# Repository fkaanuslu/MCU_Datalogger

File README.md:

# MCU_Datalogger

Schematic Layout first page

Schematic Layout second page [Connectors.sch]

PCB Layout

3D view frontside

3D view backside

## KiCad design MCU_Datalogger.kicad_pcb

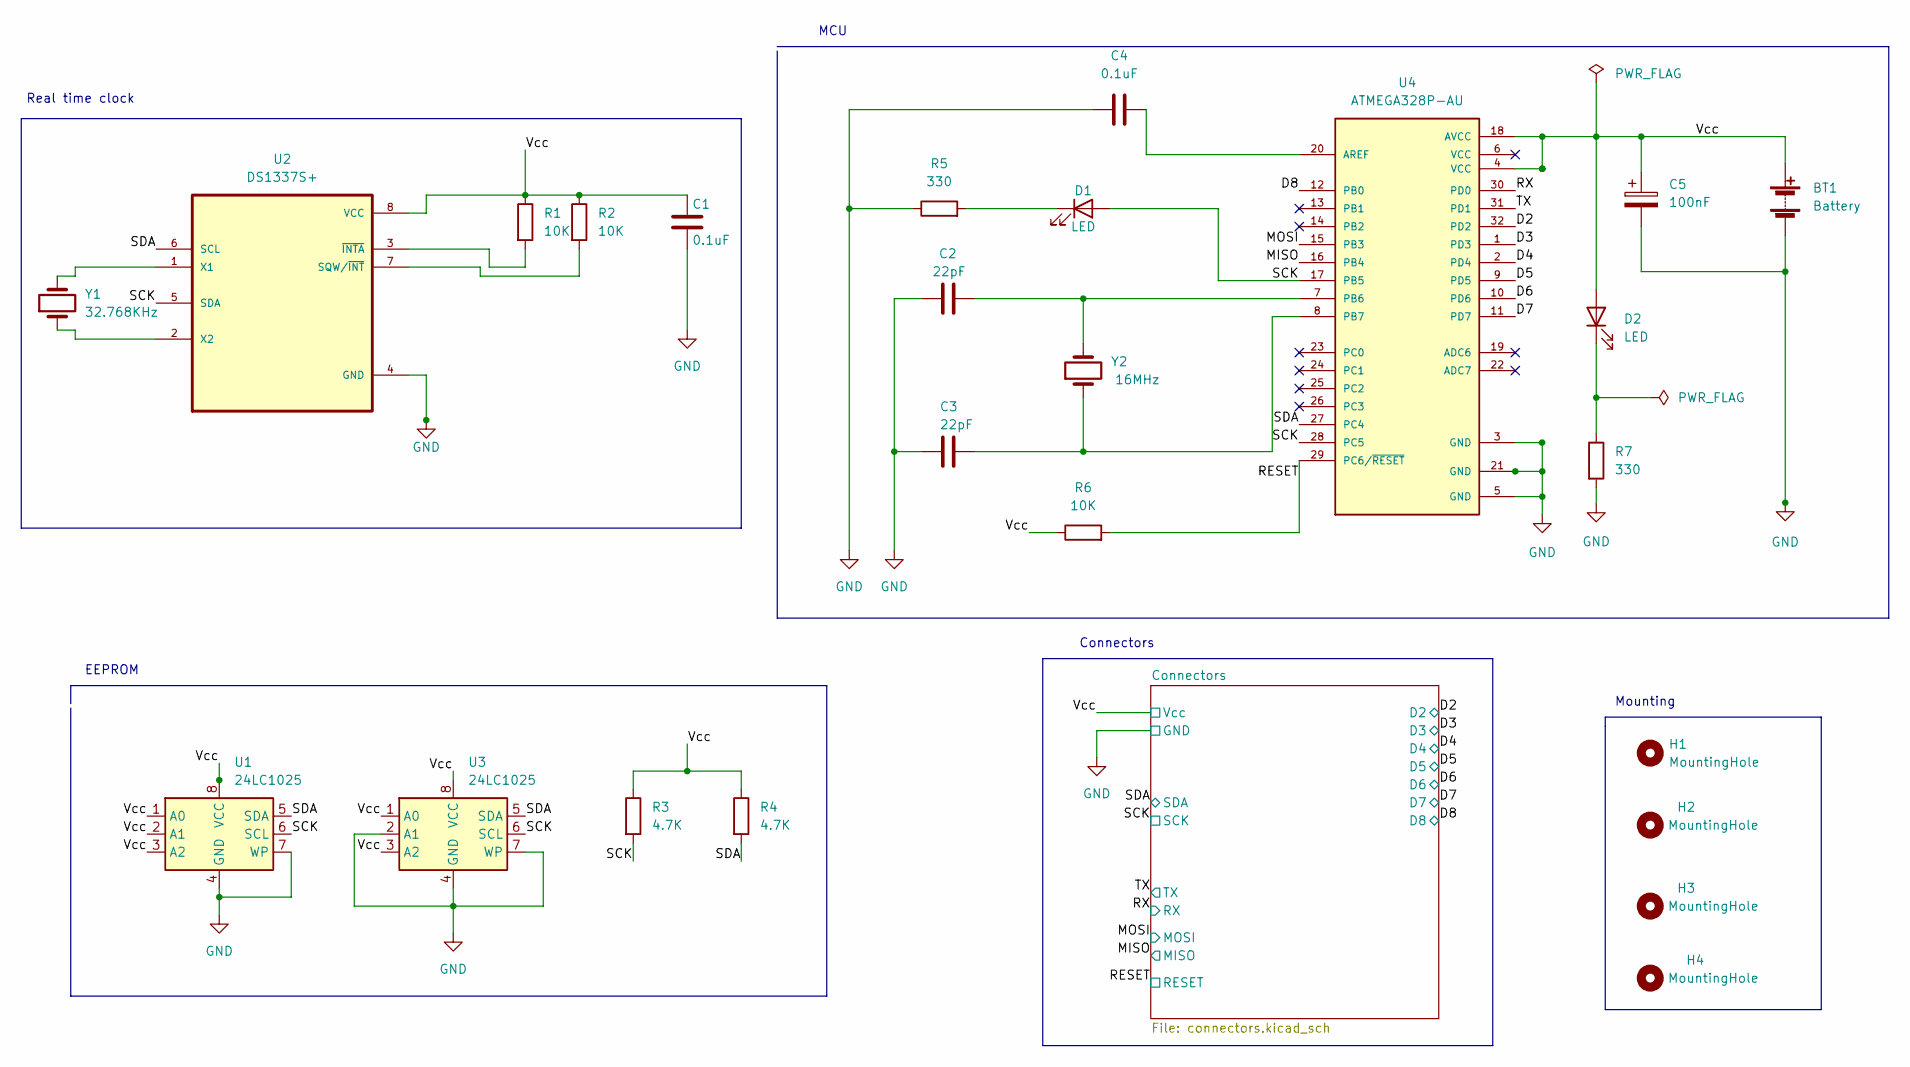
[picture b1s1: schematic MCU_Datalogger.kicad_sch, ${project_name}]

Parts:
BT1: Battery; PinHeader_1x02_P2.54mm_Vertical
C1, C4: 0.1uF; C_0805_2012Metric
C2, C3: 22pF; C_0805_2012Metric
C5: 100nF; C_0805_2012Metric
D1, D2: LED; LED_0805_2012Metric
H1, H2, H3, H4: MountingHole; MountingHole_2.1mm
R1, R2, R6: 10K; R_0805_2012Metric
R3, R4: 4.7K; R_0805_2012Metric
R5, R7: 330; R_0805_2012Metric
U1, U3: 24LC1025; SOIC-8_5.23x5.23mm_P1.27mm
U2: DS1337S+; SOIC127P600X175-8N
U4: ATMEGA328P-AU; QFP80P900X900X120-32N
Y1: 32.768KHz; Crystal_SMD_5032-2Pin_5.0x3.2mm_HandSoldering
Y2: 16MHz; Crystal_SMD_5032-2Pin_5.0x3.2mm_HandSoldering

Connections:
/D2: U4.32 (PD2); also elsewhere on the board
/D3: U4.1 (PD3); also elsewhere on the board
/D4: U4.2 (PD4); also elsewhere on the board
/D5: U4.9 (PD5); also elsewhere on the board
/D6: U4.10 (PD6); also elsewhere on the board
/D7: U4.11 (PD7); also elsewhere on the board
/D8: U4.12 (PB0); also elsewhere on the board
/MISO: U4.16 (PB4); also elsewhere on the board
/MOSI: U4.15 (PB3); also elsewhere on the board
/RESET: R6.2, U4.29 (PC6/~RESET); also elsewhere on the board
/RX: U4.30 (PD0); also elsewhere on the board
/SCK: D1.2 (A), R3.2, U1.6 (SCL), U2.5 (SDA), U3.6 (SCL), U4.17 (PB5), U4.28 (PC5); also elsewhere on the board
/SDA: R4.2, U1.5 (SDA), U2.6 (SCL), U3.5 (SDA), U4.27 (PC4); also elsewhere on the board
/TX: U4.31 (PD1); also elsewhere on the board
/Vcc: BT1.1 (+), C1.1, C5.1, D2.2 (A), R1.1, R2.1, R3.1, R4.1, R6.1, U1.1 (A0), U1.2 (A1), U1.3 (A2), U1.8 (VCC), U2.8 (VCC), U3.1 (A0), U3.3 (A2), U3.8 (VCC), U4.4 (VCC), U4.18 (AVCC); also elsewhere on the board
GND: BT1.2 (-), C1.2, C2.1, C3.2, C4.1, C5.2, R5.1, R7.2, U1.4 (GND), U1.7 (WP), U2.4 (GND), U3.2 (A1), U3.4 (GND), U3.7 (WP), U4.3 (GND), U4.5 (GND), U4.21 (GND); also elsewhere on the board
unnamed: C2.2, U4.7 (PB6), Y2.2
unnamed: C3.1, U4.8 (PB7), Y2.1
unnamed: C4.2, U4.20 (AREF)
unnamed: D1.1 (K), R5.2
unnamed: D2.1 (K), R7.1
unnamed: R1.2, U2.3 (~INTA)
unnamed: R2.2, U2.7 (SQW/~INT)
unnamed: U2.1 (X1), Y1.2
unnamed: U2.2 (X2), Y1.1

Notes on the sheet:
Real time clock
Mounting
MCU
EEPROM
Connectors

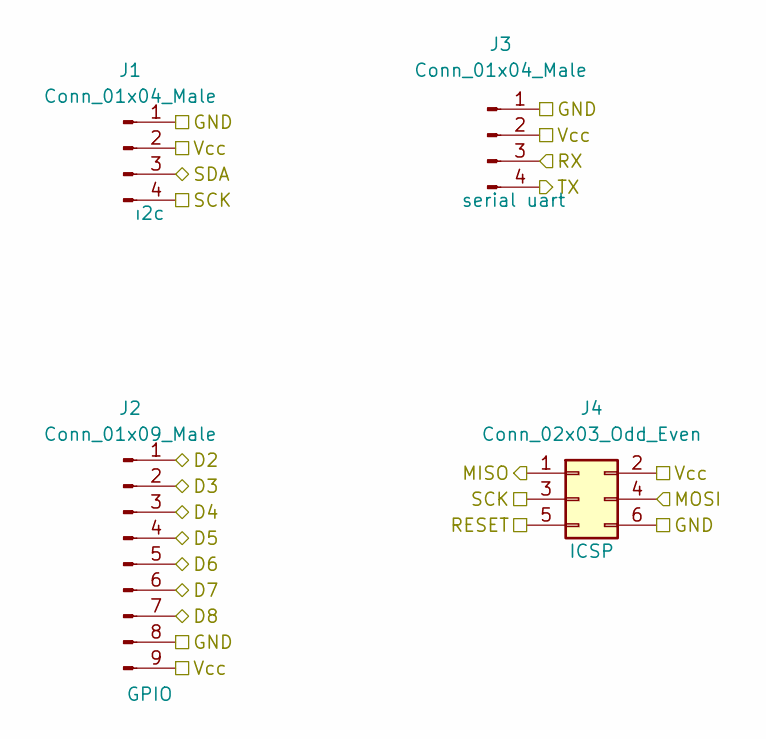
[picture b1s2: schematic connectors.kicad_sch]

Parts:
J1, J3: Conn_01x04_Male; PinHeader_1x04_P2.54mm_Vertical
J2: Conn_01x09_Male; PinHeader_1x09_P2.54mm_Vertical
J4: Conn_02x03_Odd_Even; PinHeader_2x03_P2.54mm_Vertical

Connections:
/D2: J2.1; also elsewhere on the board
/D3: J2.2; also elsewhere on the board
/D4: J2.3; also elsewhere on the board
/D5: J2.4; also elsewhere on the board
/D6: J2.5; also elsewhere on the board
/D7: J2.6; also elsewhere on the board
/D8: J2.7; also elsewhere on the board
/MISO: J4.1; also elsewhere on the board
/MOSI: J4.4; also elsewhere on the board
/RESET: J4.5; also elsewhere on the board
/RX: J3.3; also elsewhere on the board
/SCK: J1.4, J4.3; also elsewhere on the board
/SDA: J1.3; also elsewhere on the board
/TX: J3.4; also elsewhere on the board
/Vcc: J1.2, J2.9, J3.2, J4.2; also elsewhere on the board
GND: J1.1, J2.8, J3.1, J4.6; also elsewhere on the board

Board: 2 copper layers, 29 parts (0 on the bottom side), 25 nets, no tracks yet.

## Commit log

2022-07-19 delete
2022-07-19 first push
2022-07-19 commit3
2022-07-19 tekrar
2022-07-20 commit 2
